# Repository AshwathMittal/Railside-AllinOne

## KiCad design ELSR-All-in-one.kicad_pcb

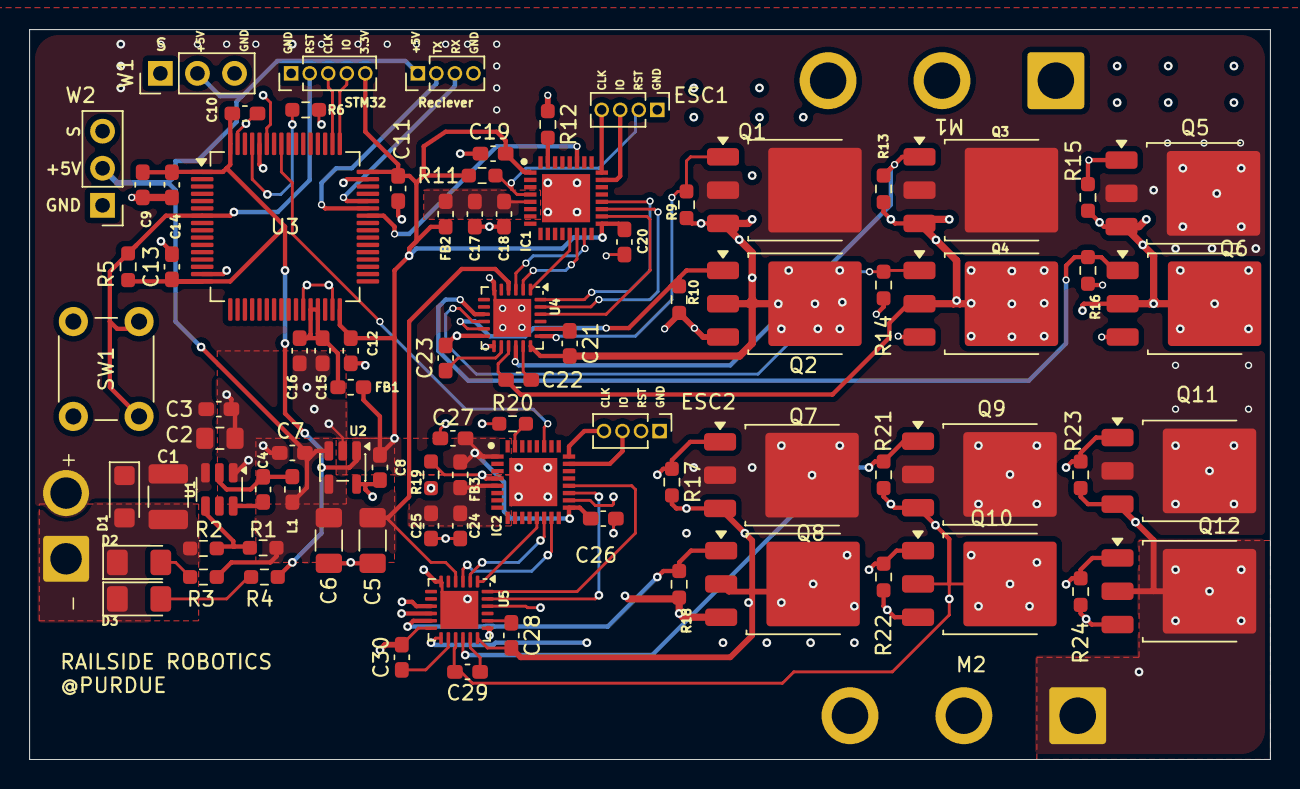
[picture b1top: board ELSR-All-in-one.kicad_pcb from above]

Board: 4 copper layers, 85.0 x 50.0 mm, 88 parts (0 on the bottom side), 66 nets.

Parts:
BATTERY: V_Bat; SolderWire-1.5sqmm_1x02_P6mm_D1.7mm_OD3mm
C1: 470uF; C_1210_3225Metric_Pad1.33x2.70mm_HandSolder
C2: 10u; C_0805_2012Metric_Pad1.18x1.45mm_HandSolder
C3, C4, C9, C10, C11, C12: 0.1u; C_0603_1608Metric_Pad1.08x0.95mm_HandSolder
C5, C6: 22u; C_1206_3216Metric_Pad1.33x1.80mm_HandSolder
C7, C8, C16: 1u; C_0603_1608Metric_Pad1.08x0.95mm_HandSolder
C13: 4.7u; C_0603_1608Metric_Pad1.08x0.95mm_HandSolder
C14: 100n; C_0603_1608Metric_Pad1.08x0.95mm_HandSolder
C15: 10n; C_0603_1608Metric_Pad1.08x0.95mm_HandSolder
C17, C19, C20, C21, C22, C23, C24, C26, C27, C28, C29, C30: 100nF; C_0603_1608Metric_Pad1.08x0.95mm_HandSolder
C18, C25: 1uF; C_0603_1608Metric_Pad1.08x0.95mm_HandSolder
D1: TVS Diode; D_SMF
D2, D3: LED; LED_1206_3216Metric_Pad1.42x1.75mm_HandSolder
ESC1, ESC2: Conn_01x04_Pin; PinHeader_1x04_P1.27mm_Vertical
FB1, FB2, FB3: FerriteBead; L_0603_1608Metric_Pad1.05x0.95mm_HandSolder
IC1, IC2: AT32F421K8U7; QFN50P500X500X80-33N-D
L1: 15u; L_0603_1608Metric_Pad1.05x0.95mm_HandSolder
M1, M2: Conn_01x03_Pin; SolderWire-2sqmm_1x03_P7.8mm_D2mm_OD3.9mm
Q1, Q2, Q3, Q4, Q5, Q6, Q7, Q8, Q9, Q10, Q11, Q12: Q_NMOS_SGD; TO-252-3_TabPin2
R1: 100K; R_0603_1608Metric_Pad0.98x0.95mm_HandSolder
R2: 13.3K; R_0603_1608Metric_Pad0.98x0.95mm_HandSolder
R3, R4: 150; R_0603_1608Metric_Pad0.98x0.95mm_HandSolder
R5, R9, R10, R11, R12, R13, R14, R15, R16, R17, R18, R19, R20, R21, R22, R23, R24: 10K; R_0603_1608Metric_Pad0.98x0.95mm_HandSolder
R6: 10k; R_0603_1608Metric_Pad0.98x0.95mm_HandSolder
Reciever: Conn_01x04_Socket; PinHeader_1x04_P1.27mm_Vertical
STM32: Conn_01x05_Pin; PinHeader_1x05_P1.27mm_Vertical
SW1: SW_Push; SW_PUSH_6mm_H4.3mm
U1: TPS54202DDC; SOT-23-6
U2: TPS7A20xxxDQN; SOT-23-5
U3: STM32G431RBTx; LQFP-64_10x10mm_P0.5mm
U4, U5: FD6288Q; QFN-24-1EP_4x4mm_P0.5mm_EP2.6x2.6mm
W1, W2: Conn_01x03_Pin; PinHeader_1x03_P2.54mm_Vertical

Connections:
+3.3VA: C15.2, C16.2, FB1.2, U3.28 (VREF+), U3.29 (VDDA)
+5V: C5.1, C6.1, C7.1, L1.2, R1.1, R3.2, Reciever.1, U2.3 (EN), U2.4 (IN), U4.4 (VCC), U5.4 (VCC), W1.2, W2.2
/ESC1/A_HIGH: IC1.18 (PA8), U4.22 (HIN1)
/ESC1/A_LOW: IC1.13 (PA7), U4.1 (LIN1)
/ESC1/B_HIGH: IC1.19 (PA9), U4.23 (HIN2)
/ESC1/B_LOW: IC1.14 (PB0), U4.2 (LIN2)
/ESC1/C_HIGH: IC1.20 (PA10), U4.24 (HIN3)
/ESC1/C_LOW: IC1.15 (PB1), U4.3 (LIN3)
/ESC1/G_AH: Q1.1 (G), R9.1, U4.19 (HO1)
/ESC1/G_AL: Q2.1 (G), R10.1, U4.11 (LO1)
/ESC1/G_BH: Q3.1 (G), R13.1, U4.16 (HO2)
/ESC1/G_BL: Q4.1 (G), R14.1, U4.10 (LO2)
/ESC1/G_CH: Q5.1 (G), R15.1, U4.13 (HO3)
/ESC1/G_CL: Q6.1 (G), R16.1, U4.9 (LO3)
/ESC1/M_A: C21.2, M1.3, Q1.3 (S), Q2.2 (D), R9.2, U4.18 (VS1)
/ESC1/M_B: C22.2, M1.2, Q3.3 (S), Q4.2 (D), R13.2, U4.15 (VS2)
/ESC1/M_C: C23.2, M1.1, Q5.3 (S), Q6.2 (D), R15.2, U4.12 (VS3)
/ESC1/nrst: ESC1.2, IC1.4 (NRST), R11.2
/ESC1/swclk: ESC1.4, IC1.24 (PA14)
/ESC1/swdio: ESC1.3, IC1.23 (PA13)
/ESC2/A_HIGH: IC2.18 (PA8), U5.22 (HIN1)
/ESC2/A_LOW: IC2.13 (PA7), U5.1 (LIN1)
/ESC2/B_HIGH: IC2.19 (PA9), U5.23 (HIN2)
/ESC2/B_LOW: IC2.14 (PB0), U5.2 (LIN2)
/ESC2/C_HIGH: IC2.20 (PA10), U5.24 (HIN3)
/ESC2/C_LOW: IC2.15 (PB1), U5.3 (LIN3)
/ESC2/G_AH: Q7.1 (G), R17.1, U5.19 (HO1)
/ESC2/G_AL: Q8.1 (G), R18.1, U5.11 (LO1)
/ESC2/G_BH: Q9.1 (G), R21.1, U5.16 (HO2)
/ESC2/G_BL: Q10.1 (G), R22.1, U5.10 (LO2)
/ESC2/G_CH: Q11.1 (G), R23.1, U5.13 (HO3)
/ESC2/G_CL: Q12.1 (G), R24.1, U5.9 (LO3)
/ESC2/M_A: C28.2, M2.3, Q7.3 (S), Q8.2 (D), R17.2, U5.18 (VS1)
/ESC2/M_B: C29.2, M2.2, Q9.3 (S), Q10.2 (D), R21.2, U5.15 (VS2)
/ESC2/M_C: C30.2, M2.1, Q11.3 (S), Q12.2 (D), R23.2, U5.12 (VS3)
/ESC2/nrst: ESC2.2, IC2.4 (NRST), R19.2
/ESC2/swclk: ESC2.4, IC2.24 (PA14)
/ESC2/swdio: ESC2.3, IC2.23 (PA13)
/STM32/RX: Reciever.3, U3.44 (USART1_RX)
/STM32/TX: Reciever.2, U3.43 (USART1_TX)
D_1: IC1.27 (PB4), U3.42 (PA8)
D_2: IC2.27 (PB4), U3.57 (PB4)
unnamed: D2.2 (A), R3.1
unnamed: D3.2 (A), R4.1
unnamed: IC1.31 (BOOT0), R12.2
unnamed: C17.2, C18.2, FB2.1, IC1.5 (VDDA)
unnamed: IC2.31 (BOOT0), R20.2
unnamed: C24.2, C25.2, FB3.1, IC2.5 (VDDA)
unnamed: C4.1, U1.6 (BOOT)
unnamed: R1.2, R2.1, U1.4 (FB)
unnamed: C4.2, L1.1, U1.2 (SW)
unnamed: R6.1, U3.61 (PB8)
unnamed: C21.1, U4.20 (VB1)
unnamed: C22.1, U4.17 (VB2)
unnamed: C23.1, U4.14 (VB3)
unnamed: C28.1, U5.20 (VB1)
unnamed: C29.1, U5.17 (VB2)
unnamed: C30.1, U5.14 (VB3)
SWCLK: STM32.3, U3.50 (PA14)
SWDIO: STM32.4, U3.49 (PA13)
VDD: C8.1, C9.2, C10.2, C11.2, C12.2, C13.1, C14.1, C19.1, C20.2, C26.1, C27.2, FB1.1, FB2.2, FB3.2, IC1.1 (VDD_1), IC1.17 (VDD_2), IC2.1 (VDD_1), IC2.17 (VDD_2), R4.2, R5.2, R11.1, R19.1, STM32.5, U2.1 (OUT), U3.1 (VBAT), U3.16 (VDD), U3.32 (VDD), U3.48 (VDD), U3.64 (VDD)
VSS: BATTERY.1, C1.1, C2.2, C3.2, C5.2, C6.2, C7.2, C8.2, C9.1, C10.1, C11.1, C12.1, C13.2, C14.2, C15.1, C16.1, C17.1, C18.1, C19.2, C20.1, C24.1, C25.1, C26.2, C27.1, D1.2 (A2), D2.1 (K), D3.1 (K), ESC1.1, ESC2.1, IC1.33 (VSS/VSSA), IC2.33 (VSS/VSSA), Q2.3 (S), Q4.3 (S), Q6.3 (S), Q8.3 (S), Q10.3 (S), Q12.3 (S), R2.2, R6.2, R10.2, R12.1, R14.2, R16.2, R18.2, R20.1, R22.2, R24.2, Reciever.4, STM32.1, SW1.2, U1.1 (GND), U2.2 (GND), U2.5 (Pad), U3.15 (VSS), U3.27 (VSSA), U3.31 (VSS), U3.47 (VSS), U3.63 (VSS), U4.6 (COM), U4.25 (GND), U5.6 (COM), U5.25 (GND), W1.3, W2.1
V_BAT: BATTERY.2, C1.2, C2.1, C3.1, D1.1 (A1), Q1.2 (D), Q3.2 (D), Q5.2 (D), Q7.2 (D), Q9.2 (D), Q11.2 (D), U1.3 (VIN)
W1_PWM: U3.59 (PB6), W1.1
W2_PWM: U3.60 (PB7), W2.3
nrst: R5.1, STM32.2, SW1.1, U3.7 (PG10)

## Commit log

2026-06-21 first
2026-06-22 updated to 4 layers and cleared several drc violations
2026-06-23 Almost Done
2026-06-23 Updated PCB Design and footprints
